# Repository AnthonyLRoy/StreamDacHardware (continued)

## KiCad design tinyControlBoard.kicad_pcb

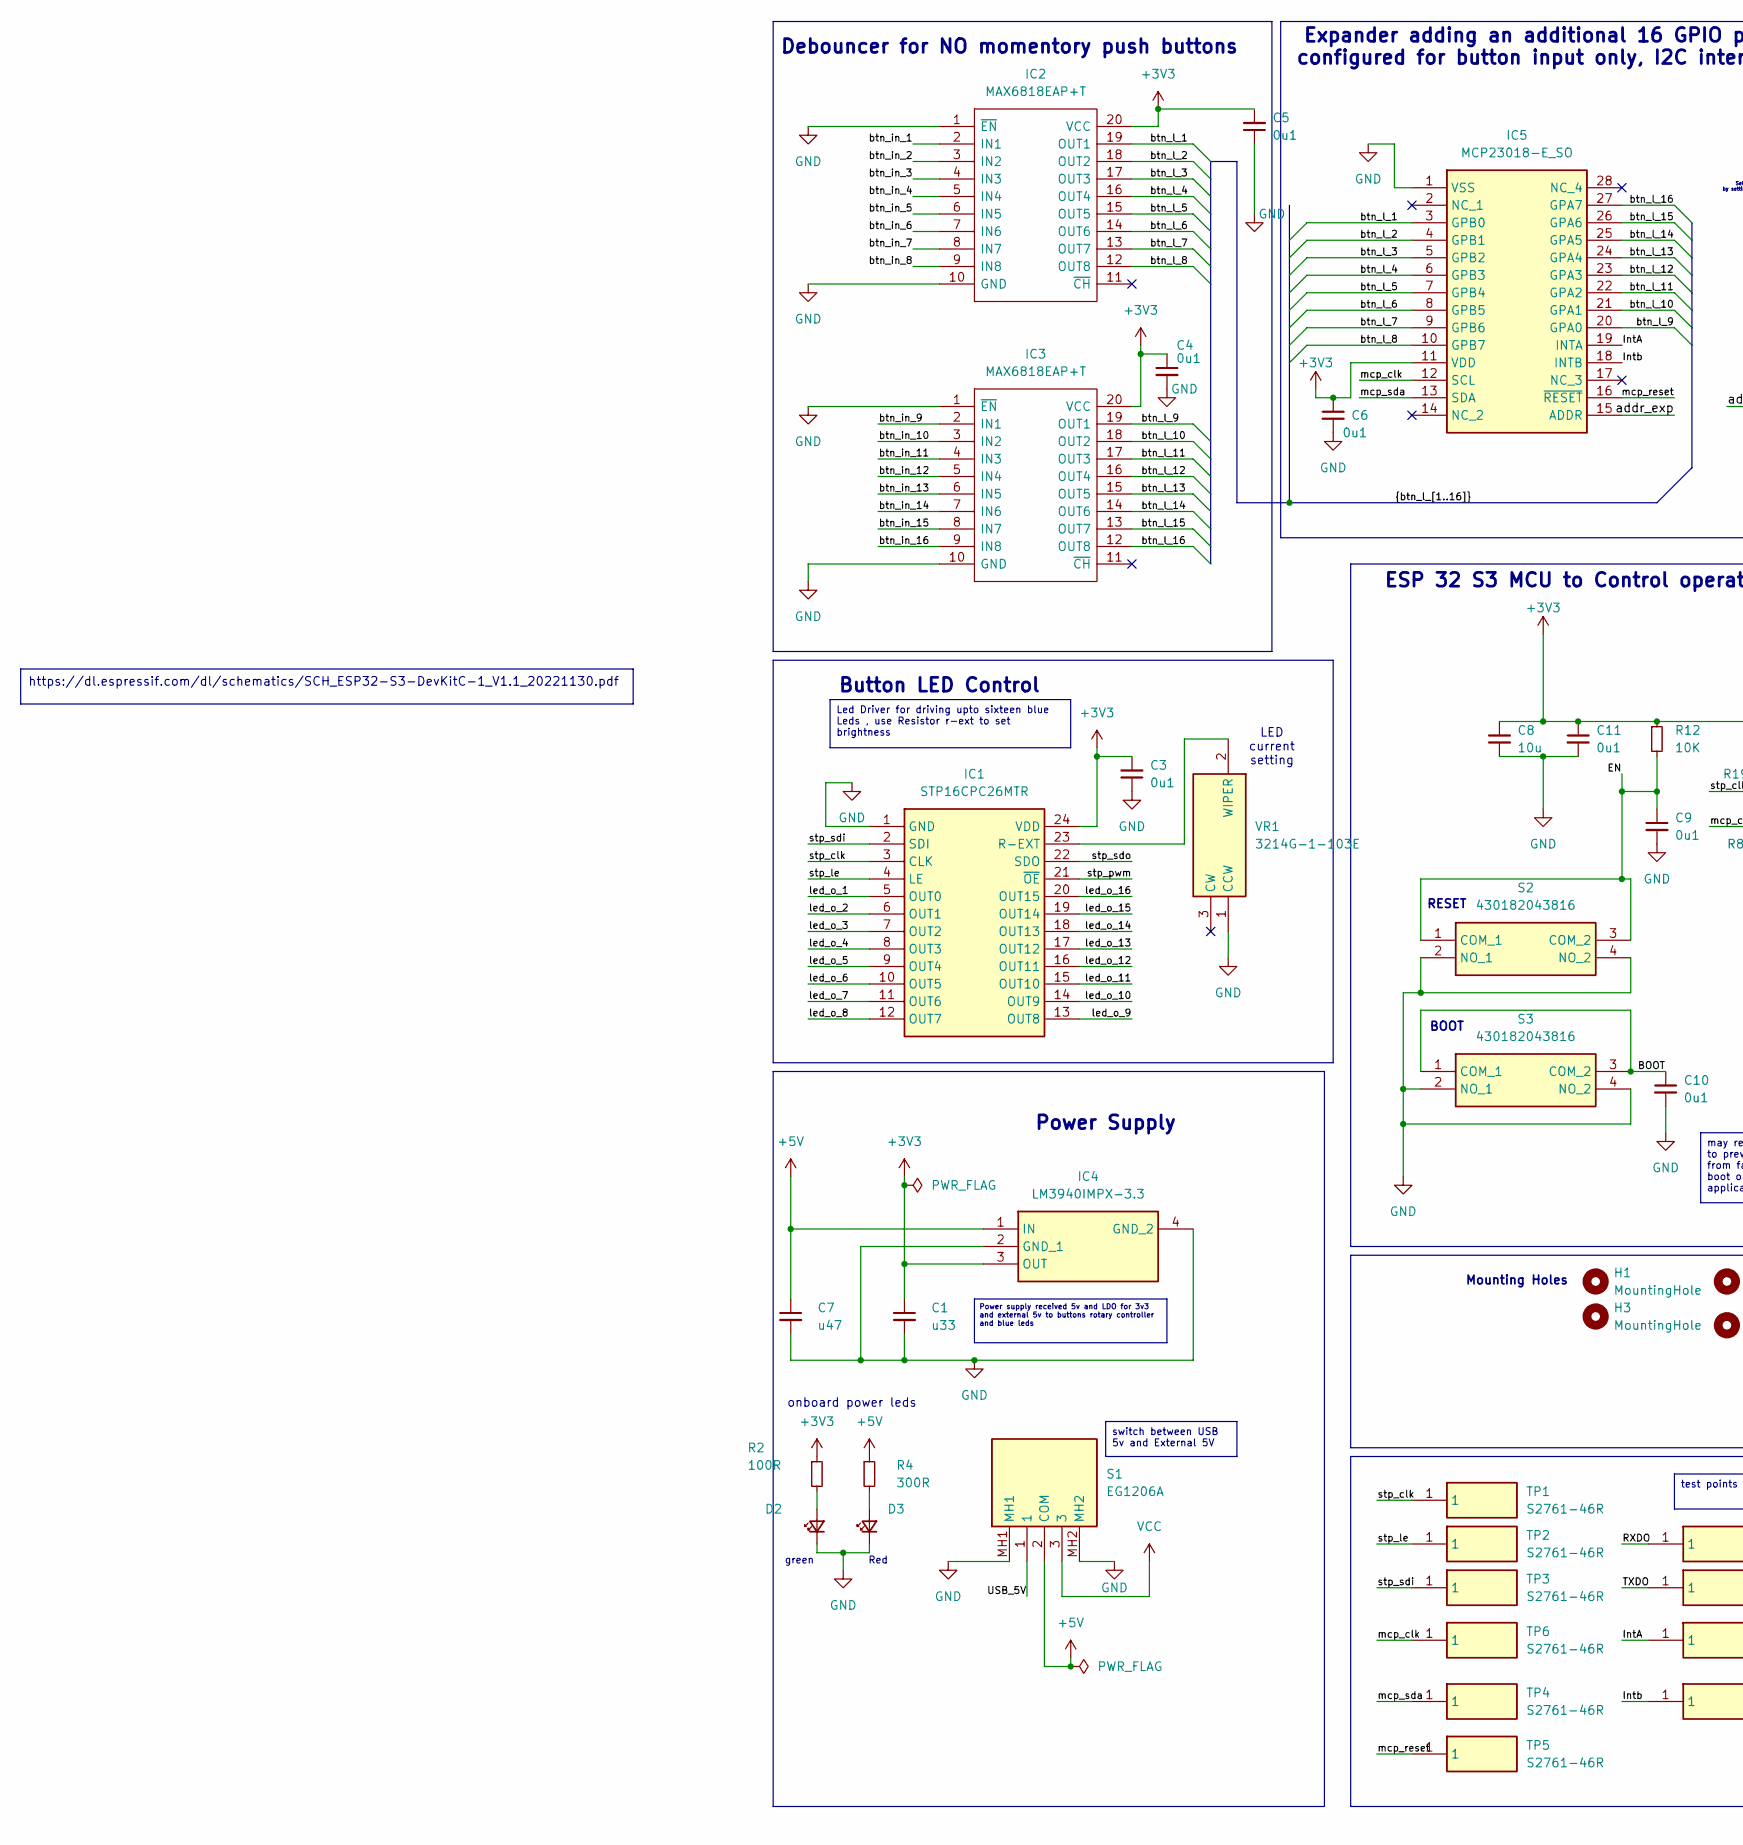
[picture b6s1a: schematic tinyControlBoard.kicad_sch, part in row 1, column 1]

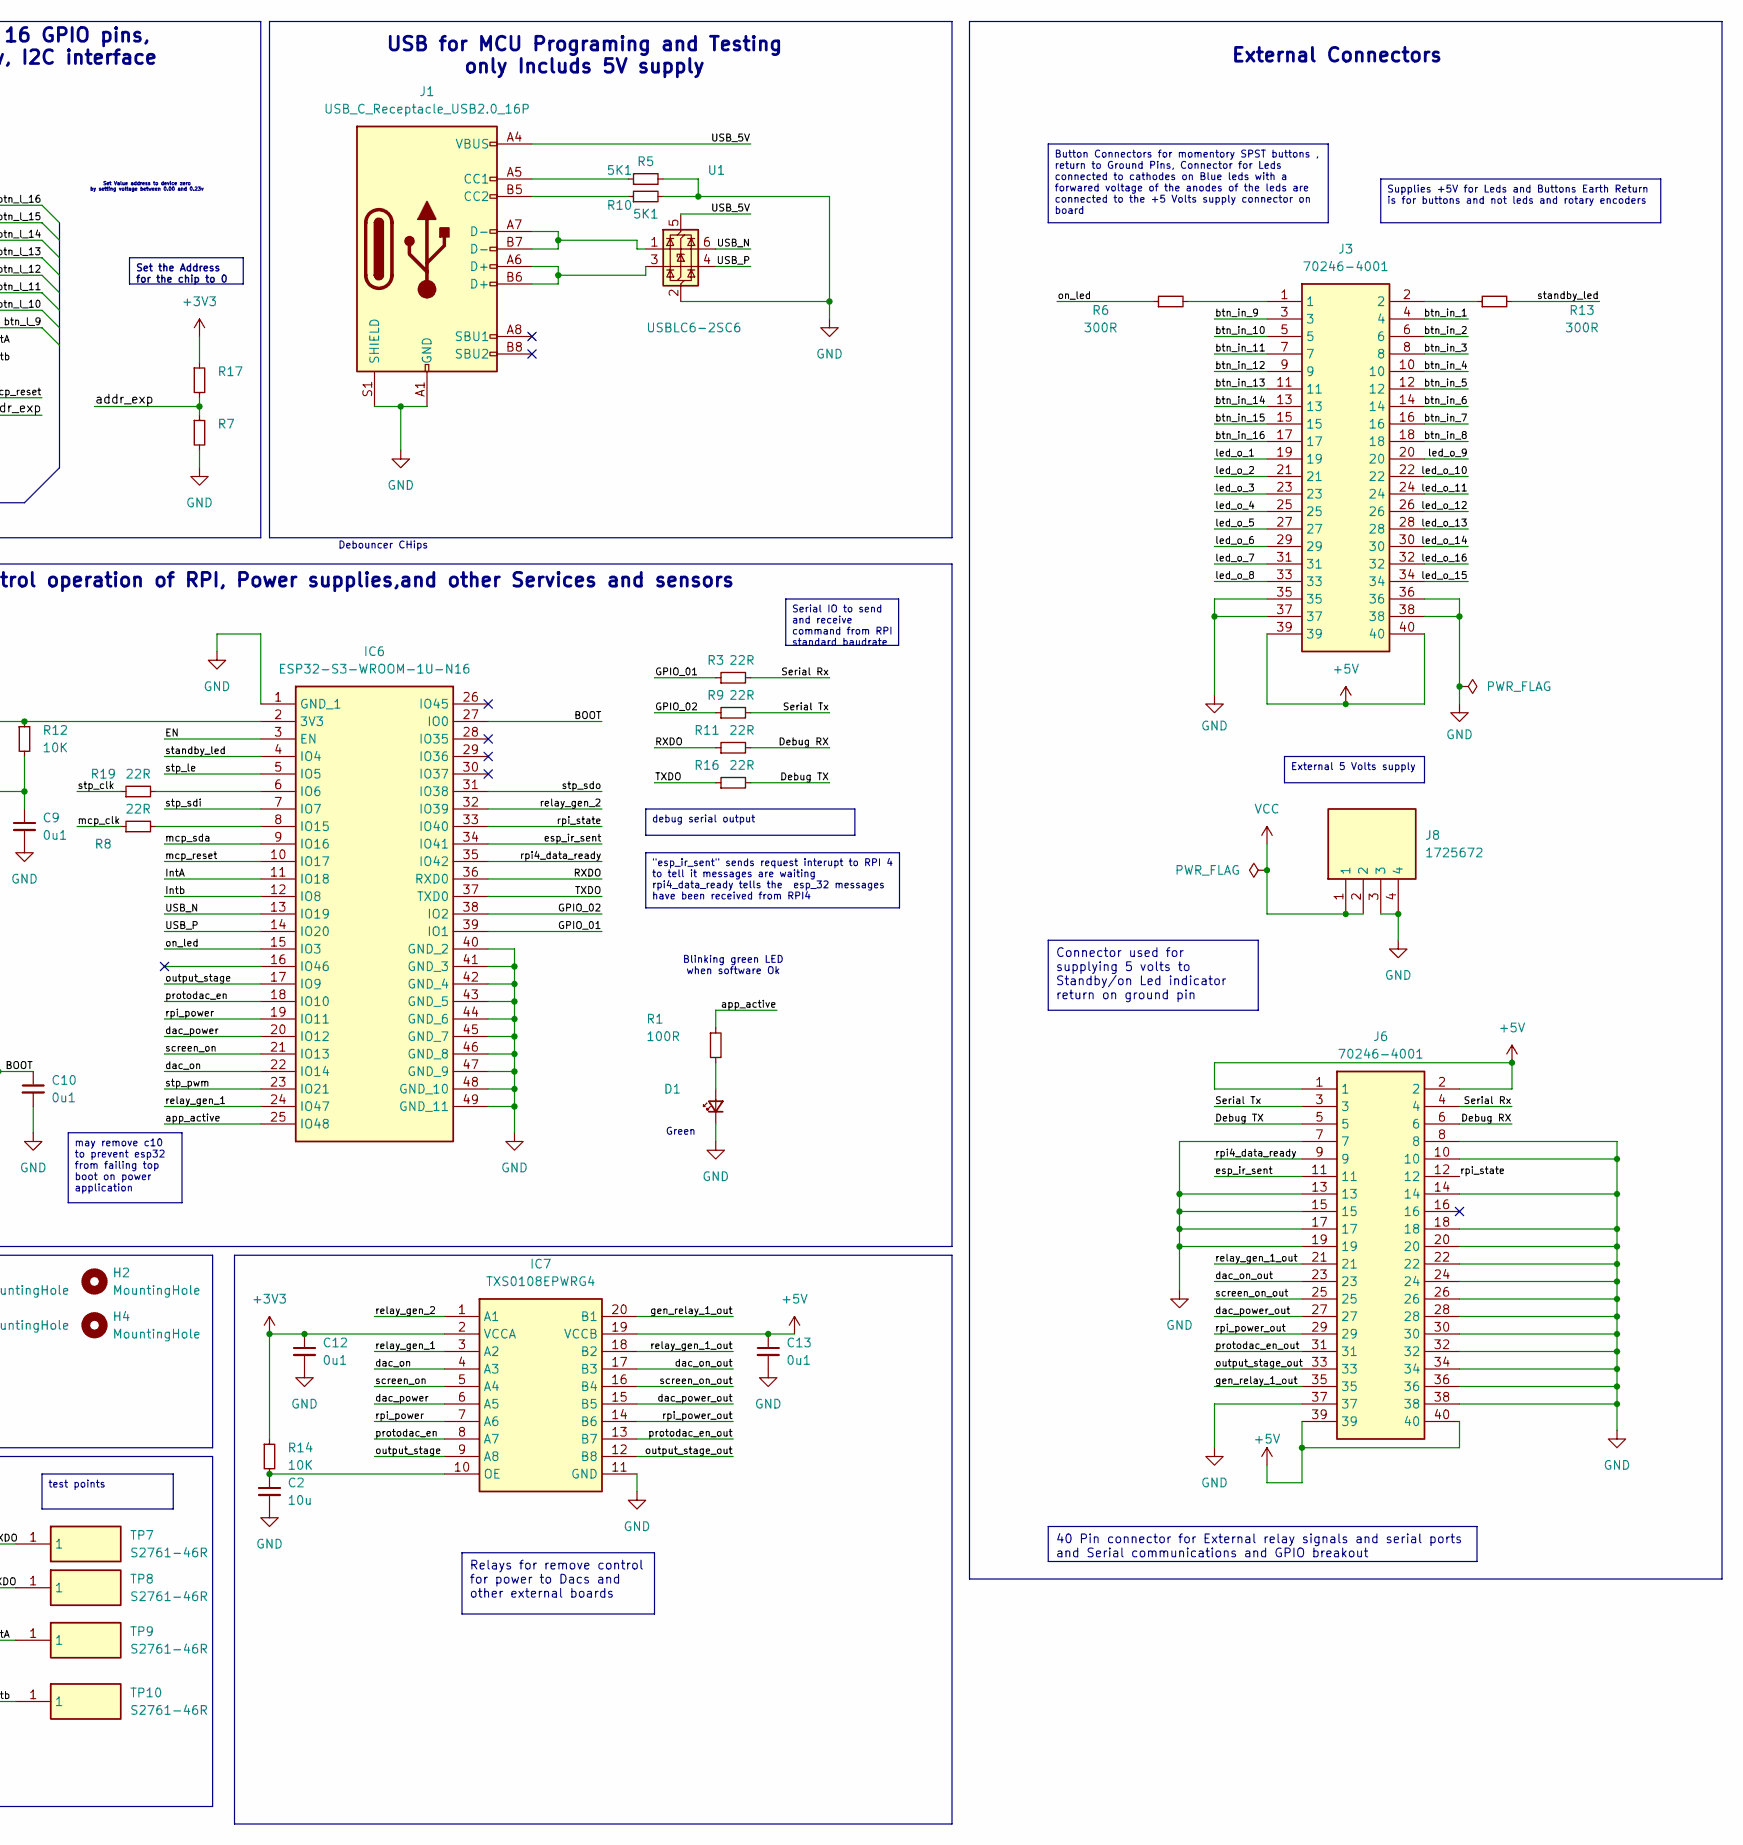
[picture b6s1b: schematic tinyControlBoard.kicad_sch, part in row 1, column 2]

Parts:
C1: u33; CAPC1608X90N; Mouser Part Number 581-0603YC334JAT2A
C2, C8: 10u; CAPC1608X90N; Mouser Part Number 581-0603YD106MAT2A
C3, C4, C5, C6, C9, C10: 0u1; CAPC1608X87N; Manufacturer_Part_Number C0603C104K4RAC3190
C7: u47; CAPC1608X90N; Mouser Part Number 81-GCM188R71C474KA5J
C11, C12, C13: 0u1; CAPC1608X87N; Mouser Part Number 80-C0603C104K4R3190
D1, D2: LG_R971-KN-1; LEDC2012X80N; Mouser Part Number 720-LGR971-KN-1
D3: LS_R976; LEDC2012X40N; Mouser Part Number 720-LSR976D5178
H1, H2, H3, H4: MountingHole; MountingHole_2.5mm
IC1: STP16CPC26MTR; SOIC127P1032X265-24N; Mouser Part Number 511-STP16CPC26MTR
IC2, IC3: MAX6818EAP+T; SSOP-20_5.3x7.2mm_P0.65mm; Manufacturer_Part_Number MAX6818EAP+T; Mouser Part Number 700-MAX6818EAPT
IC4: LM3940IMPX-3.3; SOT230P700X180-4N; Mouser Part Number 926-LM3940IMPX-33
IC5: MCP23018-E_SO; SOIC127P1030X265-28N; Mouser Part Number 579-MCP23018-E/SO
IC6: ESP32-S3-WROOM-1U-N16; ESP32S3WROOM1UN16; Mouser Part Number 356-ESP32S3WROM1UN16
IC7: TXS0108EPWRG4; SOP65P640X120-20N; Mouser Part Number 595-TXS0108EPWRG4
J1: USB_C_Receptacle_USB2.0_16P; USB_C_Receptacle_GCT_USB4105-xx-A_16P_TopMnt_Horizontal; Manufacturer_Part_Number USB4105-GF-A-120; Mouser Part Number 640-USB4105-GF-A-120
J3, J6: 70246-4001; SHDR40W64P254_2X20_5842X889X947P; Mouser Part Number 538-70246-4001
J8: 1725672; Mouser Part Number 651-1725672
R1, R2: 100R; ERJH3; Mouser Part Number 667-ERJ-H3EF1200V
R3, R8, R9, R11, R16, R19: 22R; RESC1609X55N; Mouser Part Number 667-ERJ-P03F22R0V
R4, R6, R13: 300R; ERJH3; Mouser Part Number 667-ERJ-H3ED3000V
R5, R10: 5K1; RESC1608X55N; Mouser Part Number 755-ESR03EZPJ512
R7: MCT0603PD1001DP500; RESC1608X55N; Mouser Part Number 594-MCT0603PD1001DP5
R12, R14: 10K; RESC1608X50N; Mouser Part Number 71-CRCW060310K0FKEI
R17: TNPW060315K0BEEA; RESC1608X60N; Mouser Part Number 71-TNPW060315K0BEEA
S1: EG1206A; Mouser Part Number 612-EG1206A
S2, S3: 430182043816; Mouser Part Number 710-430182043816
TP1, TP2, TP3, TP4, TP5, TP6, TP7, TP8, TP9, TP10: S2761-46R; S276146R; Mouser Part Number 855-S2761-46R
U1: USBLC6-2SC6; SOT-23-6; Manufacturer_Part_Number 511-USBLC6-2SC6; Mouser Part Number USBLC6-2SC6
VR1: 3214G-1-103E; 3214G1103E; Mouser Part Number 652-3214G-1-103E

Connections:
+3V3: C1.1, C3.2, C4.1, C5.2, C6.1, C8.1, C11.1, C12.1, IC1.24 (VDD), IC2.20 (VCC), IC3.20 (VCC), IC4.3 (OUT), IC5.11 (VDD), IC6.2 (3V3), IC7.2 (VCCA), R2.1, R12.1, R14.1, R17.1
+5V: C7.1, C13.1, IC4.1 (IN), IC7.19 (VCCB), J3.39, J3.40, J6.1, J6.2, J6.39, J6.40, R4.1, S1.2 (COM)
/BOOT: C10.1, IC6.27 (IO0), S3.1 (COM_1), S3.3 (COM_2)
/Debug RX: J6.6, R11.2
/Debug TX: J6.5, R16.2
/EN: C9.1, IC6.3 (EN), R12.2, S2.1 (COM_1), S2.3 (COM_2)
/GPIO_01: IC6.39 (IO1), R3.1
/GPIO_02: IC6.38 (IO2), R9.1
/GPIO_39: IC6.32 (IO39), IC7.1 (A1)
/IntA: IC5.19 (INTA), IC6.11 (IO18), TP9.1
/Intb: IC5.18 (INTB), IC6.12 (IO8), TP10.1
/RXDO: IC6.36 (RXD0), R11.1, TP7.1
/Serial Rx: J6.4, R3.2
/Serial Tx: J6.3, R9.2
/TXDO: IC6.37 (TXD0), R16.1, TP8.1
/USB_5V: J1.A4 (VBUS), J1.A9 (VBUS), J1.B4 (VBUS), J1.B9 (VBUS), S1.1, U1.5 (VBUS)
/USB_N: IC6.13 (IO19), U1.6 (I/O1)
/USB_P: IC6.14 (IO20), U1.4 (I/O2)
/addr_exp: IC5.15 (ADDR), R7.1, R17.2
/app_active: IC6.25 (IO48), R1.1
/btn_in_1: IC2.2 (IN1), J3.4
/btn_in_2: IC2.3 (IN2), J3.6
/btn_in_3: IC2.4 (IN3), J3.8
/btn_in_4: IC2.5 (IN4), J3.10
/btn_in_5: IC2.6 (IN5), J3.12
/btn_in_6: IC2.7 (IN6), J3.14
/btn_in_7: IC2.8 (IN7), J3.16
/btn_in_8: IC2.9 (IN8), J3.18
/btn_in_9: IC3.2 (IN1), J3.3
/btn_in_10: IC3.3 (IN2), J3.5
/btn_in_11: IC3.4 (IN3), J3.7
/btn_in_12: IC3.5 (IN4), J3.9
/btn_in_13: IC3.6 (IN5), J3.11
/btn_in_14: IC3.7 (IN6), J3.13
/btn_in_15: IC3.8 (IN7), J3.15
/btn_in_16: IC3.9 (IN8), J3.17
/btn_l_1: IC2.19 (OUT1), IC5.3 (GPB0)
/btn_l_2: IC2.18 (OUT2), IC5.4 (GPB1)
/btn_l_3: IC2.17 (OUT3), IC5.5 (GPB2)
/btn_l_4: IC2.16 (OUT4), IC5.6 (GPB3)
/btn_l_5: IC2.15 (OUT5), IC5.7 (GPB4)
/btn_l_6: IC2.14 (OUT6), IC5.8 (GPB5)
/btn_l_7: IC2.13 (OUT7), IC5.9 (GPB6)
/btn_l_8: IC2.12 (OUT8), IC5.10 (GPB7)
/btn_l_9: IC3.19 (OUT1), IC5.20 (GPA0)
/btn_l_10: IC3.18 (OUT2), IC5.21 (GPA1)
/btn_l_11: IC3.17 (OUT3), IC5.22 (GPA2)
/btn_l_12: IC3.16 (OUT4), IC5.23 (GPA3)
/btn_l_13: IC3.15 (OUT5), IC5.24 (GPA4)
/btn_l_14: IC3.14 (OUT6), IC5.25 (GPA5)
/btn_l_15: IC3.13 (OUT7), IC5.26 (GPA6)
/btn_l_16: IC3.12 (OUT8), IC5.27 (GPA7)
/dac_on: IC6.22 (IO14), IC7.4 (A3)
/dac_on_out: IC7.17 (B3), J6.23
/esp_ir_sent: IC6.34 (IO41), J6.11
/gen_relay_1_out: IC7.20 (B1), J6.35
/gen_relay_2: IC6.18 (IO10), IC7.8 (A7)
/gen_relay_2_out: IC7.13 (B7), J6.31
/gen_relay_3: IC6.17 (IO9), IC7.9 (A8)
/gen_relay_3_out: IC7.12 (B8), J6.33
/gen_relay_4: IC6.24 (IO47), IC7.3 (A2)
/gen_relay_4_out: IC7.18 (B2), J6.21
/led_o_1: IC1.5 (OUT0), J3.19
/led_o_2: IC1.6 (OUT1), J3.21
/led_o_3: IC1.7 (OUT2), J3.23
/led_o_4: IC1.8 (OUT3), J3.25
/led_o_5: IC1.9 (OUT4), J3.27
/led_o_6: IC1.10 (OUT5), J3.29
/led_o_7: IC1.11 (OUT6), J3.31
/led_o_8: IC1.12 (OUT7), J3.33
/led_o_9: IC1.13 (OUT8), J3.20
/led_o_10: IC1.14 (OUT9), J3.22
/led_o_11: IC1.15 (OUT10), J3.24
/led_o_12: IC1.16 (OUT11), J3.26
/led_o_13: IC1.17 (OUT12), J3.28
/led_o_14: IC1.18 (OUT13), J3.30
/led_o_15: IC1.19 (OUT14), J3.34
/led_o_16: IC1.20 (OUT15), J3.32
/mains_power: IC6.19 (IO11), IC7.7 (A6)
/mains_power_out: IC7.14 (B6), J6.29
/mcp_clk: IC5.12 (SCL), R8.1, TP6.1
/mcp_reset: IC5.16 (~RESET), IC6.10 (IO17), TP5.1
/mcp_sda: IC5.13 (SDA), IC6.9 (IO16), TP4.1
/on_led: IC6.15 (IO3), R6.1
/rpi4_data_ready: IC6.35 (IO42), J6.9
/rpi_state: IC6.33 (IO40), J6.12
/screen_on: IC6.21 (IO13), IC7.5 (A4)
/screen_on_out: IC7.16 (B4), J6.25
/standby_led: IC6.4 (IO4), R13.2
/stp_clk: IC1.3 (CLK), R19.1, TP1.1
/stp_le: IC1.4 (LE), IC6.5 (IO5), TP2.1
/stp_pwm: IC1.21 (~OE), IC6.23 (IO21)
/stp_sdi: IC1.2 (SDI), IC6.7 (IO7), TP3.1
/stp_sdo: IC1.22 (SDO), IC6.31 (IO38)
/switch_dac: IC6.20 (IO12), IC7.6 (A5)
/switch_dac_out: IC7.15 (B5), J6.27
GND: C1.2, C2.2, C3.1, C4.2, C5.1, C6.2, C7.2, C8.2, C9.2, C10.2, C11.2, C12.2, C13.2, D1.1 (K), D2.1 (K), D3.1 (K), IC1.1 (GND), IC2.1 (~EN), IC2.10 (GND), IC3.1 (~EN), IC3.10 (GND), IC4.2 (GND_1), IC4.4 (GND_2), IC5.1 (VSS), IC6.1 (GND_1), IC6.40 (GND_2), IC6.41 (GND_3), IC6.42 (GND_4), IC6.43 (GND_5), IC6.44 (GND_6), IC6.45 (GND_7), IC6.46 (GND_8), IC6.47 (GND_9), IC6.48 (GND_10), IC6.49 (GND_11), IC7.11 (GND), J1.A1 (GND), J1.A12 (GND), J1.B1 (GND), J1.B12 (GND), J1.S1 (SHIELD), J3.35, J3.36, J3.37, J3.38, J6.7, J6.8, J6.10, J6.13, J6.14, J6.15, J6.17, J6.18, J6.19, J6.20, J6.22, J6.24, J6.26, J6.28, J6.30, J6.32, J6.34, J6.36, J6.37, J6.38, J8.3, J8.4, R5.2, R7.2, R10.2, S1.MH1, S1.MH2, S2.2 (NO_1), S2.4 (NO_2), S3.2 (NO_1), S3.4 (NO_2), U1.2 (GND), VR1.1 (CCW)
unnamed: D1.2 (A), R1.2
unnamed: D2.2 (A), R2.2
unnamed: D3.2 (A), R4.2
unnamed: IC1.23 (R-EXT), VR1.2 (WIPER)
unnamed: IC6.6 (IO6), R19.2
unnamed: IC6.8 (IO15), R8.2
unnamed: C2.1, IC7.10 (OE), R14.2
unnamed: J1.A5 (CC1), R5.1
unnamed: J1.B5 (CC2), R10.1
unnamed: J1.A6 (D+), J1.B6 (D+), U1.3 (I/O2)
unnamed: J1.A7 (D-), J1.B7 (D-), U1.1 (I/O1)
unnamed: J3.1, R6.2
unnamed: J3.2, R13.1
VCC: J8.1, J8.2, S1.3

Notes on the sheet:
Connector used for supplying 5 volts to Standby/on Led indicator return on ground pin
https://dl.espressif.com/dl/schematics/SCH_ESP32-S3-DevKitC-1_V1.1_20221130.pdf
External 5 Volts supply
Supplies +5V for Leds and Buttons Earth Return is for buttons and not leds and rotary encoders
Serial IO to send and receive command from RPI standard baudrate
40 Pin connector for External relay signals and serial ports and Serial communications and GPIO breakout
debug serial output
switch between USB 5v and External 5V
Power supply received 5v and LDO for 3v3 and external 5v to buttons rotary controller and blue leds
Set the Address for the chip to 0
"esp_ir_sent" sends request interupt to RPI 4 to tell it messages are waiting rpi4_data_ready tells the esp_32 messages have been received from RPI4
Relays for remove control for power to Dacs and other external boards
test points
Button Connectors for momentory SPST buttons , return to Ground Pins, Connector for Leds connected to cathodes on Blue leds with a forwared voltage of the anodes of the leds are connected to the +5 Volts supply connector on board
Led Driver for driving upto sixteen blue Leds , use Resistor r-ext to set brightness
may remove c10 to prevent esp32 from failing top boot on power application
Green
Set Value address to device zero by setting voltage between 0.00 and 0.23v
onboard power leds
BOOT
USB for MCU Programing and Testing only Includs 5V supply
Debouncer CHips
Mounting Holes
Expander adding an additional 16 GPIO pins, configured for button input only, I2C interface
Debouncer for NO momentory push buttons
RESET
Power Supply
Button LED Control
Red
ESP 32 S3 MCU to Control operation of RPI, Power supplies,and other Services and sensors
Blinking green LED when software Ok
green
LED current setting
External Connectors

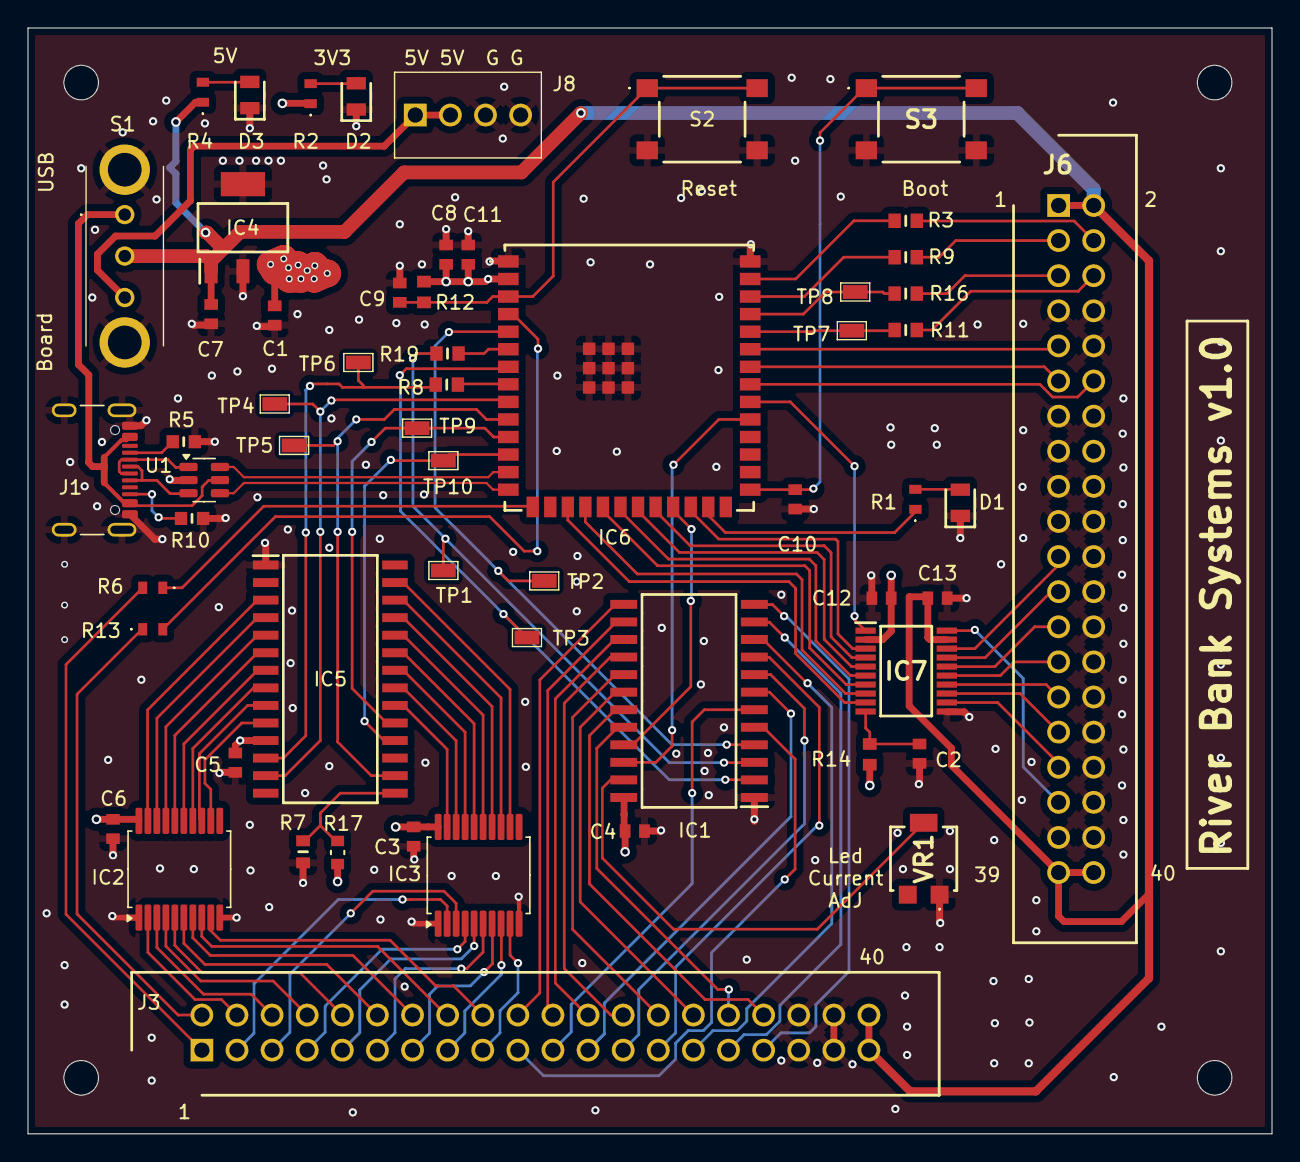
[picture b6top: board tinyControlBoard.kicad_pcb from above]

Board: 4 copper layers, 90.0 x 80.0 mm, 63 parts (0 on the bottom side), 111 nets.

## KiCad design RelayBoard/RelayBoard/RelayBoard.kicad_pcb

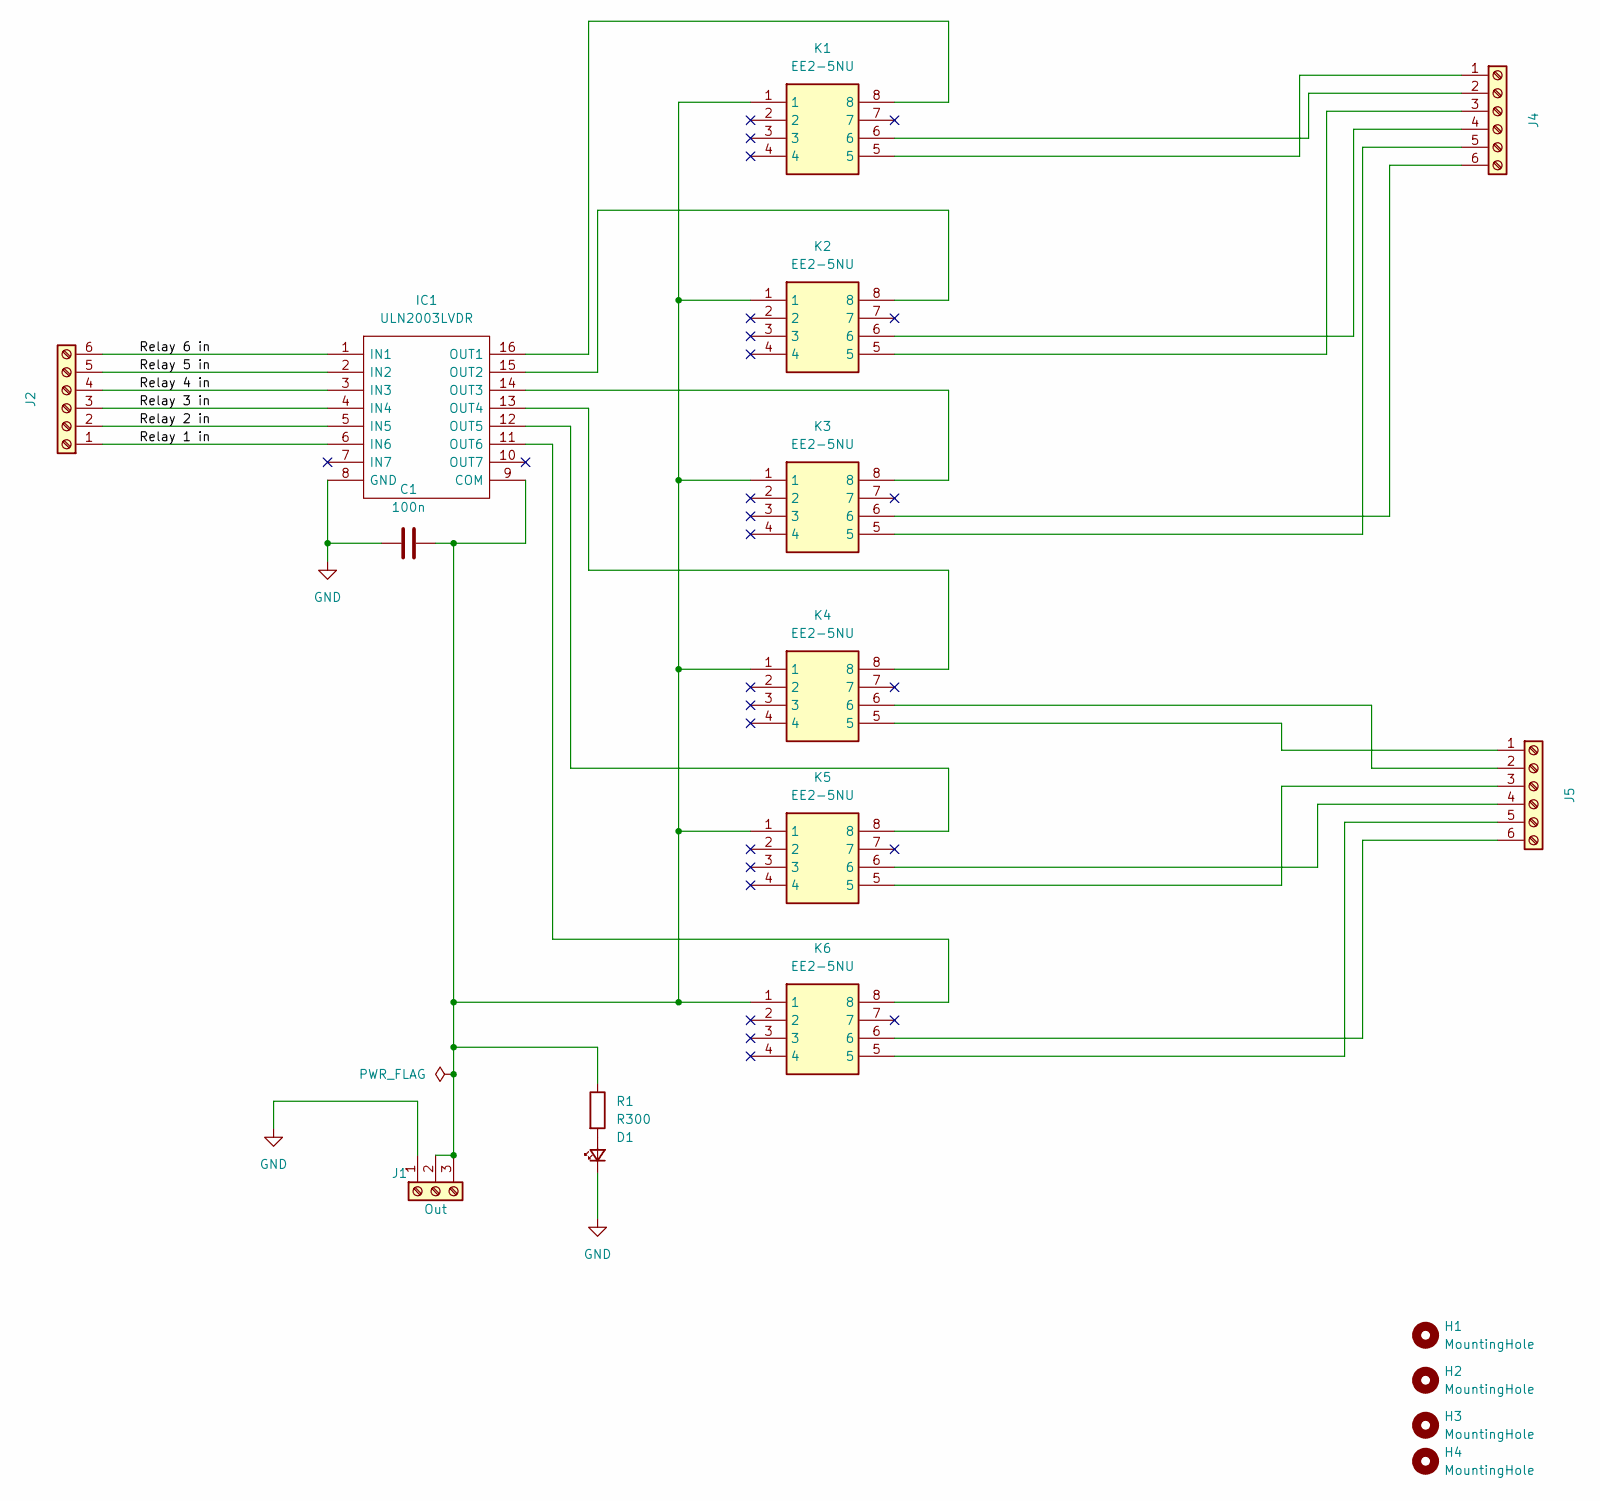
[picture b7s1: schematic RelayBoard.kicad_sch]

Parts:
C1: 100n; C_0805_2012Metric_Pad1.18x1.45mm_HandSolder
D1: LS_R976; LEDC2012X40N; Mouser Part Number 720-LSR976D5178
H1, H2, H3, H4: MountingHole; MountingHole_2.7mm_M2.5
IC1: ULN2003LVDR; SOIC127P780X200-16N; Manufacturer_Part_Number ULN2003LVDR; Mouser Part Number 595-ULN2003LVDR
J1: Out; PinHeader_1x03_P2.54mm_Vertical
J2, J4, J5: Buffer; PinHeader_1x06_P2.54mm_Vertical
K1, K2, K3, K4, K5, K6: EE2-5NU; Mouser Part Number 80-EE2-5NU
R1: R300; R_0603_1608Metric_Pad0.98x0.95mm_HandSolder

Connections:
/Relay 1 in: IC1.6 (IN6), J2.1
/Relay 2 in: IC1.5 (IN5), J2.2
/Relay 3 in: IC1.4 (IN4), J2.3
/Relay 4 in: IC1.3 (IN3), J2.4
/Relay 5 in: IC1.2 (IN2), J2.5
/Relay 6 in: IC1.1 (IN1), J2.6
GND: C1.1, D1.1 (K), IC1.8 (GND), J1.1
unnamed: D1.2 (A), R1.2
unnamed: C1.2, IC1.9 (COM), J1.2, J1.3, K1.1, K2.1, K3.1, K4.1, K5.1, K6.1, R1.1
unnamed: IC1.16 (OUT1), K1.8
unnamed: IC1.15 (OUT2), K2.8
unnamed: IC1.14 (OUT3), K3.8
unnamed: IC1.13 (OUT4), K4.8
unnamed: IC1.12 (OUT5), K5.8
unnamed: IC1.11 (OUT6), K6.8
unnamed: J4.1, K1.5
unnamed: J4.2, K1.6
unnamed: J4.3, K2.5
unnamed: J4.4, K2.6
unnamed: J4.5, K3.5
unnamed: J4.6, K3.6
unnamed: J5.1, K4.5
unnamed: J5.2, K4.6
unnamed: J5.3, K5.5
unnamed: J5.4, K5.6
unnamed: J5.5, K6.5
unnamed: J5.6, K6.6

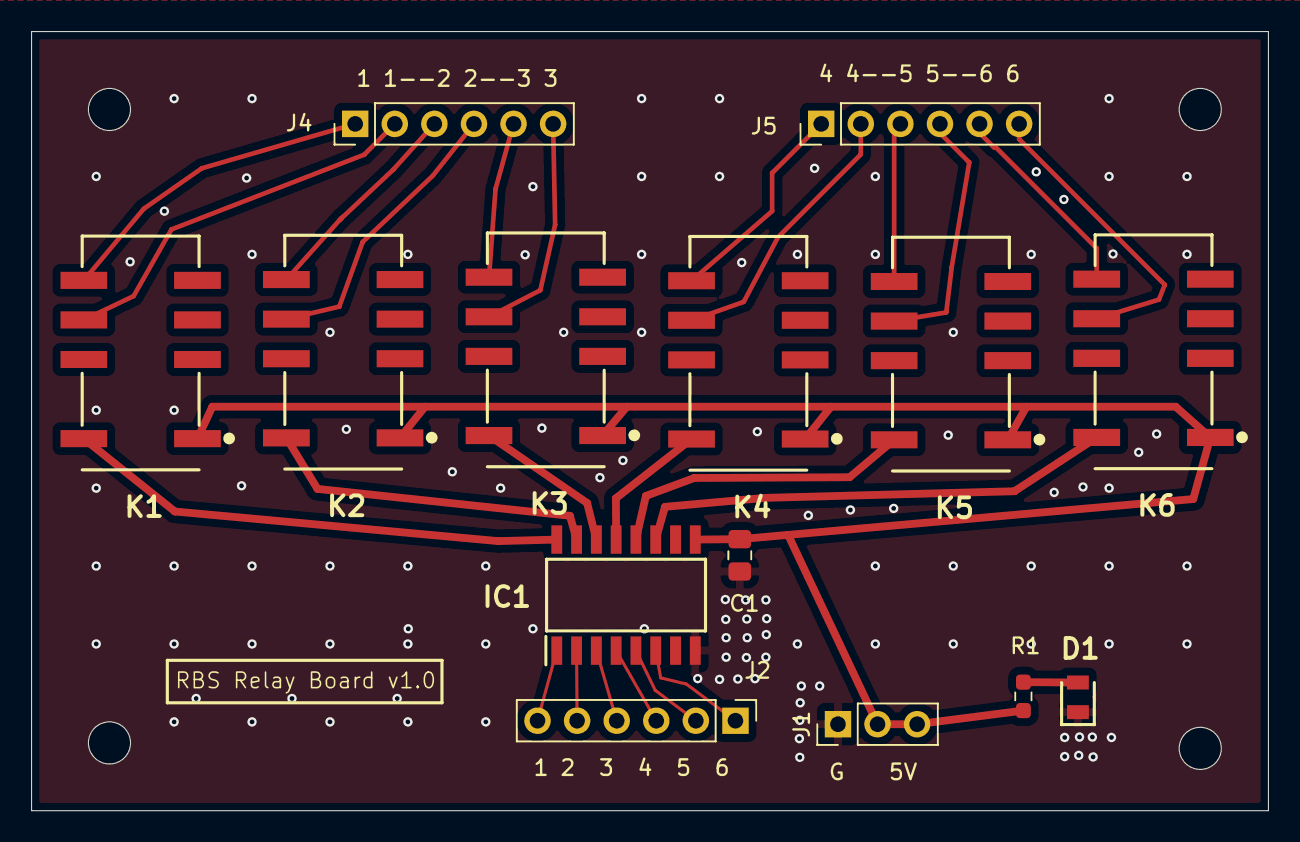
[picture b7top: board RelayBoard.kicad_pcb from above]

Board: 2 copper layers, 79.4 x 50.0 mm, 18 parts (0 on the bottom side), 27 nets.

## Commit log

2026-01-08 initial push
2026-01-08 removed Relay and power supples related items from board and add seperate ground plains for signal and power
2026-01-08 Test
2026-01-17 added new rpi power board
2026-01-18 update relayboard set size for RPI4
2026-01-24 add updates to se to diff
2026-01-29 updated final four boards for streamer
2026-02-22 More changes to the boards
